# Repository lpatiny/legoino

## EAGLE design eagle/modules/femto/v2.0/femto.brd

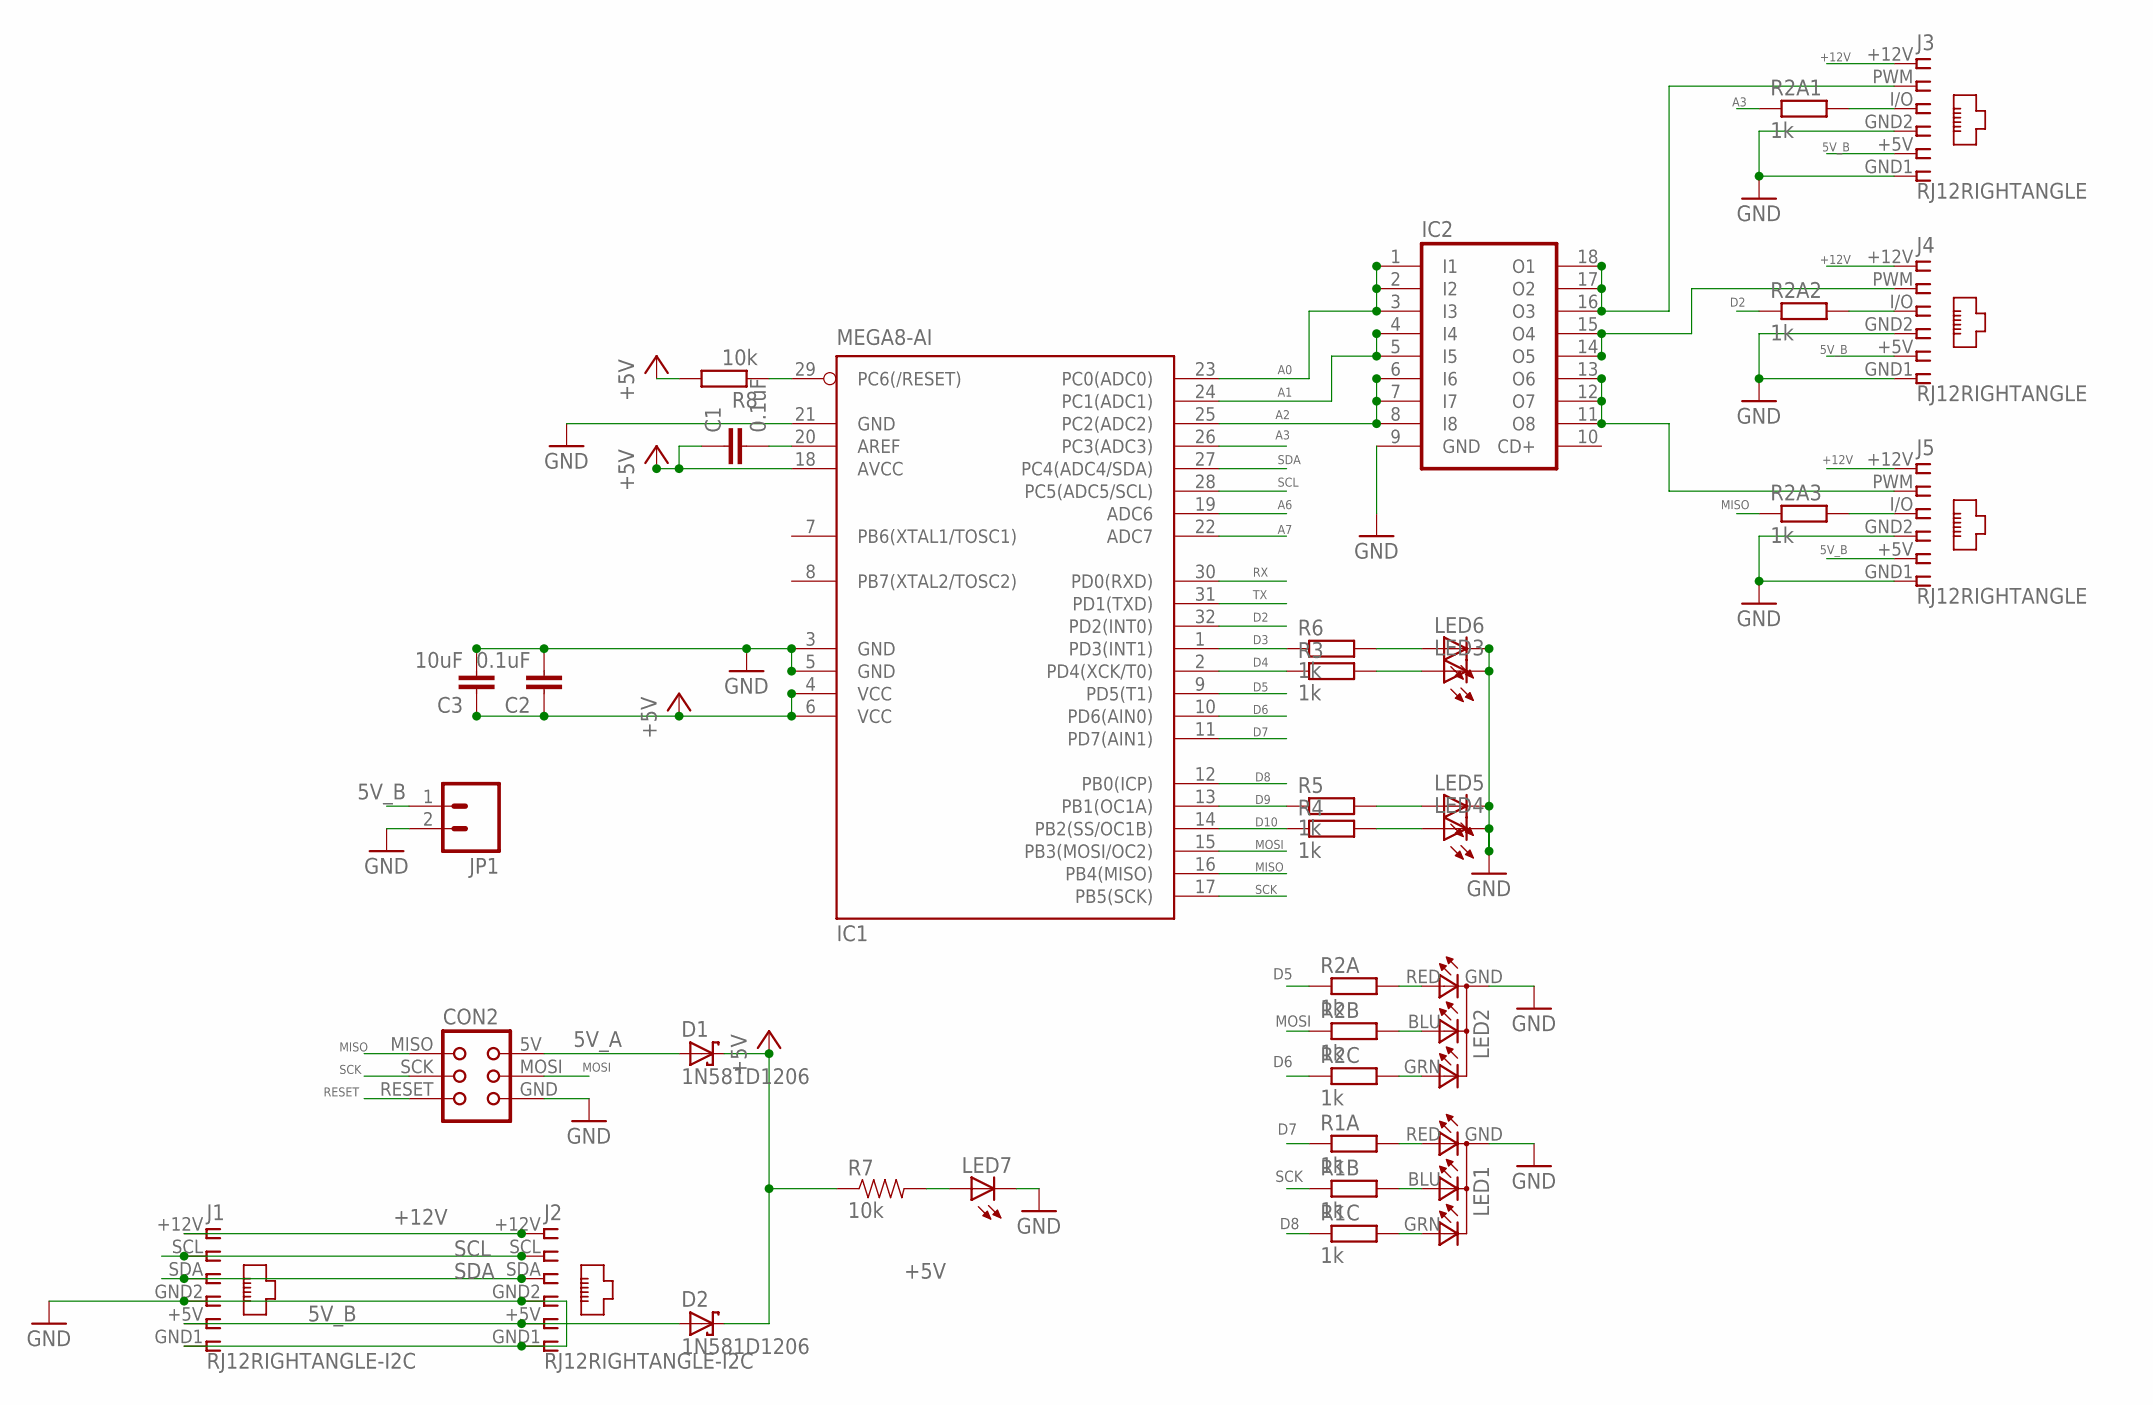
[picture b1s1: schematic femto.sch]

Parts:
C1, C2: 0.1uF; C1206
C3: 10uF; C1206
CON2: TINYISPTAG; TC2030-MCP
D1, D2: 1N581D1206; LED-1206
IC1: MEGA8-AI; TQFP32-08
IC2: ULN2803A; SO18W
J1, J2: RJ12RIGHTANGLE-I2C; RJ12-RIGHTANGLE-I2C
J3, J4, J5: RJ12RIGHTANGLE; RJ12-RIGHTANGLE
JP1: M023.5MM; SCREWTERMINAL-3.5MM-2
LED1, LED2: RGB-COMMON-CATHODE; LED-TRICOLOR-THROUGHHOLE
LED3, LED4, LED5, LED6: LED3MM
LED7: LEDCHIP-LED0603; CHIP-LED0603
R1A, R1B, R1C, R2A, R2A1, R2A2, R2A3, R2B, R2C, R3, R4, R5, R6: 1k; M1206
R7: 10k; 0603-RES
R8: 10k; M1206

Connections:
5V_A: CON2.5V (VCC), D1.A
5V_B: D2.A, J1.+5V (5), J2.+5V (5), J3.+5V (5), J4.+5V (5), J5.+5V (5), JP1.1
+5V: C1.1, C2.1, C3.1, D1.C, D2.C, IC1.4 (VCC), IC1.6 (VCC), IC1.18 (AVCC), R7.1, R8.2
+12V: J1.+12V (1), J2.+12V (1), J3.+12V (1), J4.+12V (1), J5.+12V (1)
A0: IC1.23 (PC0(ADC0)), IC2.1 (I1), IC2.2 (I2), IC2.3 (I3)
A1: IC1.24 (PC1(ADC1)), IC2.4 (I4), IC2.5 (I5)
A2: IC1.25 (PC2(ADC2)), IC2.6 (I6), IC2.7 (I7), IC2.8 (I8)
A3: IC1.26 (PC3(ADC3)), R2A1.1
A6: IC1.19 (ADC6)
A7: IC1.22 (ADC7)
D2: IC1.32 (PD2(INT0)), R2A2.1
D3: IC1.1 (PD3(INT1)), R6.1
D4: IC1.2 (PD4(XCK/T0)), R3.1
D5: IC1.9 (PD5(T1)), R2A.1
D6: IC1.10 (PD6(AIN0)), R2C.1
D7: IC1.11 (PD7(AIN1)), R1A.1
D8: IC1.12 (PB0(ICP)), R1C.1
D9: IC1.13 (PB1(OC1A)), R5.1
D10: IC1.14 (PB2(SS/OC1B)), R4.1
GND: C2.2, C3.2, CON2.GND, IC1.3 (GND), IC1.5 (GND), IC1.21 (GND), IC2.9 (GND), J1.GND1 (6), J1.GND2 (4), J2.GND1 (6), J2.GND2 (4), J3.GND1 (6), J3.GND2 (4), J4.GND1 (6), J4.GND2 (4), J5.GND1 (6), J5.GND2 (4), JP1.2, LED1.GND (A2), LED2.GND (A2), LED3.K (C), LED4.K (C), LED5.K (C), LED6.K (C), LED7.C
MISO: CON2.MISO, IC1.16 (PB4(MISO)), R2A3.1
MOSI: CON2.MOSI, IC1.15 (PB3(MOSI/OC2)), R2B.1
unnamed: LED2.RED (CRED), R2A.2
unnamed: J3.I/O (3), R2A1.2
unnamed: IC2.16 (O3), IC2.17 (O2), IC2.18 (O1), J3.PWM (2)
unnamed: C1.2, IC1.20 (AREF)
unnamed: IC2.14 (O5), IC2.15 (O4), J4.PWM (2)
unnamed: IC2.11 (O8), IC2.12 (O7), IC2.13 (O6), J5.PWM (2)
unnamed: LED2.BLU (CBLUE), R2B.2
unnamed: LED2.GRN (CGREEN), R2C.2
unnamed: J4.I/O (3), R2A2.2
unnamed: J5.I/O (3), R2A3.2
unnamed: LED7.A, R7.2
unnamed: LED3.A, R3.2
unnamed: LED1.RED (CRED), R1A.2
unnamed: LED1.BLU (CBLUE), R1B.2
unnamed: LED1.GRN (CGREEN), R1C.2
unnamed: LED6.A, R6.2
unnamed: LED5.A, R5.2
unnamed: LED4.A, R4.2
RESET: CON2.RESET, IC1.29 (PC6(/RESET)), R8.1
RX: IC1.30 (PD0(RXD))
SCK: CON2.SCK, IC1.17 (PB5(SCK)), R1B.1
SCL: IC1.28 (PC5(ADC5/SCL)), J1.SCL (2), J2.SCL (2)
SDA: IC1.27 (PC4(ADC4/SDA)), J1.SDA (3), J2.SDA (3)
TX: IC1.31 (PD1(TXD))

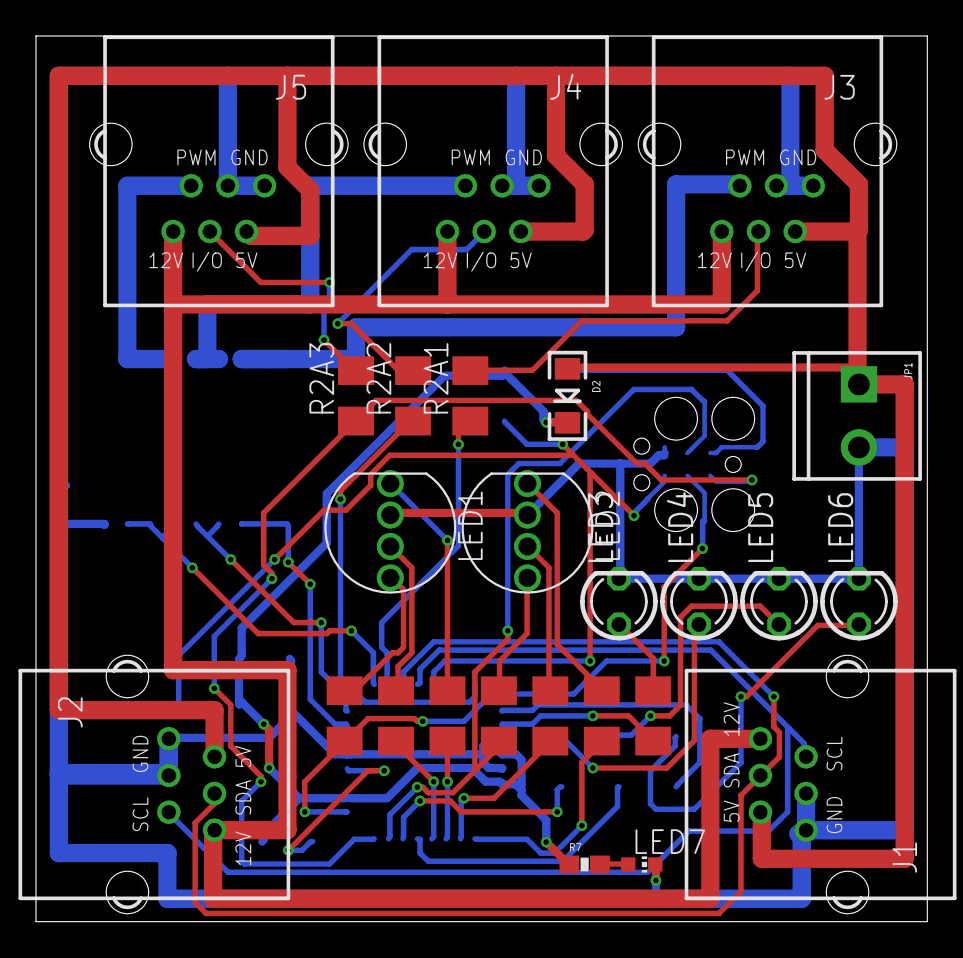
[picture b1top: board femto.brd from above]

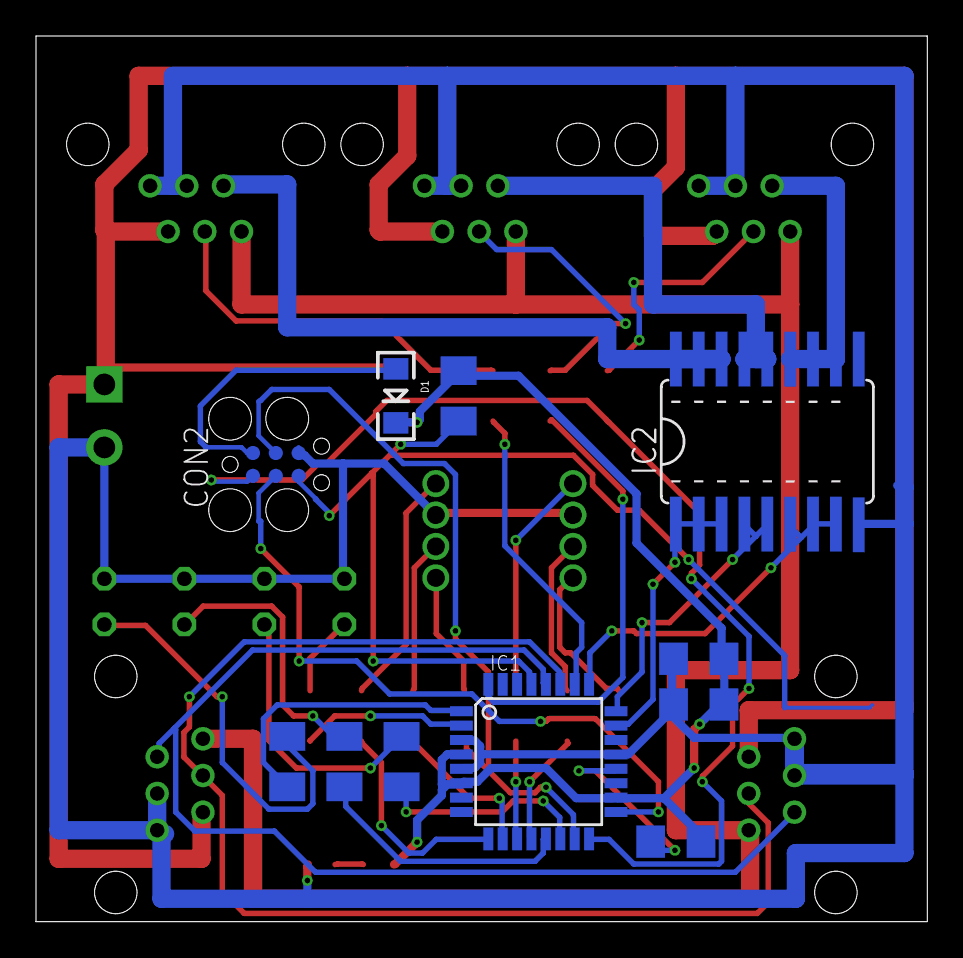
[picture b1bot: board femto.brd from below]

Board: 2 copper layers, 49.5 x 49.2 mm, 36 parts (11 on the bottom side), 42 nets.

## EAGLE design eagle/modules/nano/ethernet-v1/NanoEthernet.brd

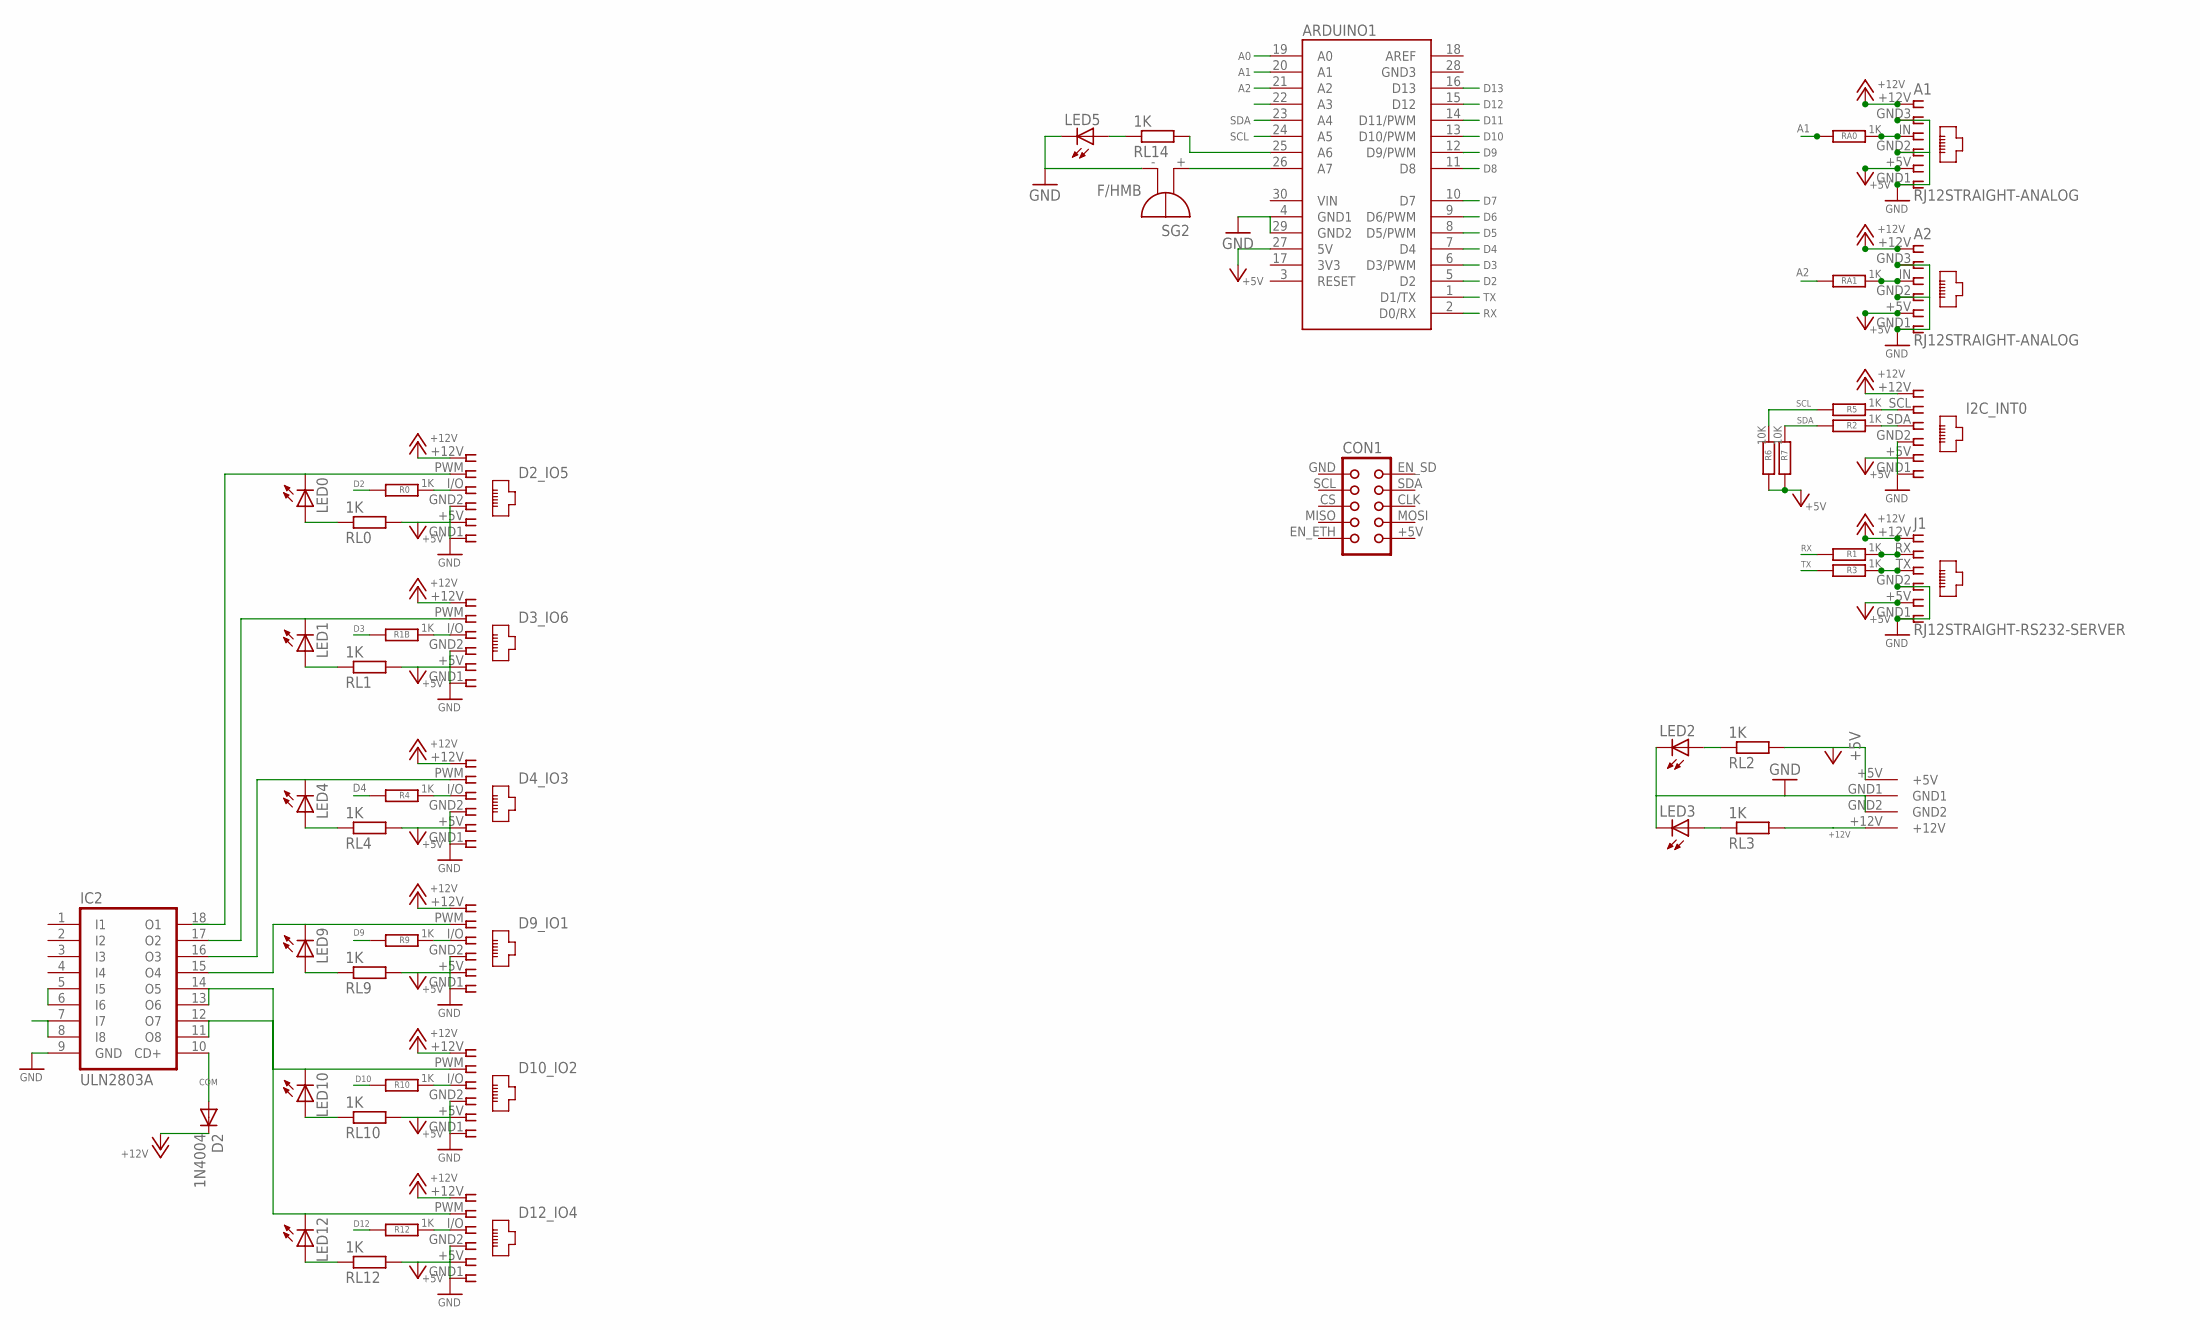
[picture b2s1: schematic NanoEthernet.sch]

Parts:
A1, A2: RJ12STRAIGHT-ANALOG; RJ12-STRAIGHT-ANALOG
ARDUINO1: ARDUINO_NANO
CON1: CON10EXT
D2: 1N4004; DO41-10
D2_IO5: IO5; RJ12-STRAIGHT
D3_IO6: IO6; RJ12-STRAIGHT
D4_IO3: IO3; RJ12-STRAIGHT
D9_IO1: IO1; RJ12-STRAIGHT
D10_IO2: IO2; RJ12-STRAIGHT
D12_IO4: IO4; RJ12-STRAIGHT
I2C_INT0: I2C; RJ12-STRAIGHT-I2C
IC2: ULN2803A; SO18W
J1: RJ12STRAIGHT-RS232-SERVER; RJ12-STRAIGHT-RS232
LED0, LED1, LED2, LED3, LED4, LED5, LED9, LED10, LED12: LED3MM
R0, R1, R1B, R2, R3, R4, R5, R9, R10, R12: 1K; M1206
R6, R7: 10K; M1206
RA0, RA1: 1K; M1206
RL0, RL1, RL2, RL3, RL4, RL9, RL10, RL12, RL14: 1K; M1206
SG2: F/HMB
U$1: KPJX-4S-S

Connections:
3V3: ARDUINO1.17 (3V3)
+5V: A1.+5V (5), A2.+5V (5), ARDUINO1.27 (5V), D2_IO5.+5V (5), D3_IO6.+5V (5), D4_IO3.+5V (5), D9_IO1.+5V (5), D10_IO2.+5V (5), D12_IO4.+5V (5), I2C_INT0.+5V (5), J1.+5V (5), R6.2, R7.2, RL0.2, RL1.2, RL2.2, RL4.2, RL9.2, RL10.2, RL12.2, U$1.+5V
+12V: A1.+12V (1), A2.+12V (1), D2.C, D2_IO5.+12V (1), D3_IO6.+12V (1), D4_IO3.+12V (1), D9_IO1.+12V (1), D10_IO2.+12V (1), D12_IO4.+12V (1), I2C_INT0.+12V (1), J1.+12V (1), RL3.2, U$1.+12V
A0: ARDUINO1.19 (A0)
A1: ARDUINO1.20 (A1), RA0.2
A2: ARDUINO1.21 (A2), RA1.2
COM: D2.A, IC2.10 (CD+)
D2: ARDUINO1.5 (D2), R0.2
D2B: D4_IO3.I/O (3), R4.1
D2B1: D9_IO1.I/O (3), R9.1
D2B2: D10_IO2.I/O (3), R10.1
D2B3: D12_IO4.I/O (3), R12.1
D2B4: I2C_INT0.SDA (3), R2.1
D2B5: J1.TX (3), R3.1
D2B6: D2_IO5.I/O (3), R0.1
D2B7: D3_IO6.I/O (3), R1B.1
D2B8: A1.IN (3), RA0.1
D2B9: A2.IN (3), RA1.1
D3: ARDUINO1.6 (D3/PWM), R1B.2
D4: ARDUINO1.7 (D4), R4.2
D5: ARDUINO1.8 (D5/PWM)
D6: ARDUINO1.9 (D6/PWM)
D7: ARDUINO1.10 (D7)
D8: ARDUINO1.11 (D8)
D9: ARDUINO1.12 (D9/PWM), R9.2
D10: ARDUINO1.13 (D10/PWM), IC2.5 (I5), IC2.6 (I6), R10.2
D11: ARDUINO1.14 (D11/PWM)
D12: ARDUINO1.15 (D12), IC2.7 (I7), IC2.8 (I8), R12.2
D13: ARDUINO1.16 (D13)
GND: A1.GND1 (6), A1.GND2 (4), A1.GND3 (2), A2.GND1 (6), A2.GND2 (4), A2.GND3 (2), ARDUINO1.4 (GND1), ARDUINO1.29 (GND2), D2_IO5.GND1 (6), D2_IO5.GND2 (4), D3_IO6.GND1 (6), D3_IO6.GND2 (4), D4_IO3.GND1 (6), D4_IO3.GND2 (4), D9_IO1.GND1 (6), D9_IO1.GND2 (4), D10_IO2.GND1 (6), D10_IO2.GND2 (4), D12_IO4.GND1 (6), D12_IO4.GND2 (4), I2C_INT0.GND1 (6), I2C_INT0.GND2 (4), IC2.9 (GND), J1.GND1 (6), J1.GND2 (4), LED2.K (C), LED3.K (C), LED5.K (C), SG2.-, U$1.GND1, U$1.GND2
unnamed: J1.RX (2), R1.1
unnamed: I2C_INT0.SCL (2), R5.1
unnamed: LED5.A, RL14.1
unnamed: LED9.A, RL9.1
unnamed: LED3.A, RL3.1
unnamed: LED4.A, RL4.1
unnamed: D4_IO3.PWM (2), IC2.16 (O3), LED4.K (C)
unnamed: ARDUINO1.25 (A6), RL14.2
unnamed: LED10.A, RL10.1
unnamed: ARDUINO1.26 (A7), SG2.+
unnamed: LED2.A, RL2.1
unnamed: D10_IO2.PWM (2), IC2.13 (O6), IC2.14 (O5), LED10.K (C)
unnamed: LED12.A, RL12.1
unnamed: D3_IO6.PWM (2), IC2.17 (O2), LED1.K (C)
unnamed: LED0.A, RL0.1
unnamed: D2_IO5.PWM (2), LED0.K (C)
unnamed: LED1.A, RL1.1
unnamed: D9_IO1.PWM (2), IC2.15 (O4), LED9.K (C)
unnamed: D12_IO4.PWM (2), IC2.11 (O8), IC2.12 (O7), LED12.K (C)
RX: ARDUINO1.2 (D0/RX), R1.2
SCL: ARDUINO1.24 (A5), R5.2, R6.1
SDA: ARDUINO1.23 (A4), R2.2, R7.1
TX: ARDUINO1.1 (D1/TX), R3.2

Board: 2 copper layers, 48 parts (18 on the bottom side), 45 nets, no tracks yet.

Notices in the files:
parts and their libraries:
lpatiny: ©2009 ROFA.cz - modified and updated by Robert Darlington ‹rdarlington@gmail.com›
SparkFun: Licensing: CC v3.0 Share-Alike You are welcome to use this library for commercial purposes.
